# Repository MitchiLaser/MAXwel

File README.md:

# MAXwel

**MAX ii Workbench for Education and Learning - MAXwel**

MAXwel is a cheap and simple FPGA development board made for educational purposes.
It is based in a low-cost Altera MAX ii Chip (EPM240), containing 240 logic elements, 8Kbits of RAM and 32Kbits of flash memory.
The board is equipped with 8 switches, 4 push-buttons, 16 LEDs (divided into rows A and B of 8 LEDs each) and four 7-segment displays.
It also contains a 50MHz oscillator and a 14,7456 MHz oscillator as a clock source.
The board is programmed through a USB Blaster JTAG interface with the pin-header located on the board.

All schematics and PCB files are available in the `hardware` directory.

## Documentation and project template

[The user documentation is available in the `docs` directory](docs/main.pdf) and on the [landing page](https://mitchilaser.github.io/MAXwel/).

A [template for an empty VHDL project](template/vhdl) with correct pin assignments is available [in the `template` directory](template/).
The directory also contains a [template for a schematic based circuit design](template/schematic).
All templates are intended to be used with the [Quartus](https://fpgasoftware.intel.com/) software from Intel.

## What else?

There are also some features for hardcore enthusiasts.

### Lab Course

My university uses this FPGA board for a students lab course. There is a directory containing the reference designs for the lab course exercises.
The lab course exercises require the students to draw schematic diagrams in the Quartus software within a predefined template file.
The [Quartus](https://fpgasoftware.intel.com/) software only offers the logic symbols in the US style within the schematic editor.
This directory also offers EU style symbols for the project symbol library of the Quartus software.

### Overlay

**This project is currently under heavy development.**

The Overlay is an open FPGA architecture for open tools and user designs that is intended to run on the MAX ii chip, in essence an "FPGA on a FPGA".
The main goal of the Overlay is to provide a simple and easy to use platform for learning and experimenting with FPGA synthesis technology. 
Once the overlay is synthesizes and loaded into the MAX ii chip, it will be possible to load user designs into the overlay, without the need to re-synthesize the overlay itself.
This allows for a high level of flexibility and experimentation, as well as a way to learn about FPGA synthesis and design without the need for the closed source tools from the FPGA manufacturer.
Emulating an FPGA inside an FPGA takes up a lot of resources. Therefore the Overlay is not made for practical use cases outside of learning and experimentation.

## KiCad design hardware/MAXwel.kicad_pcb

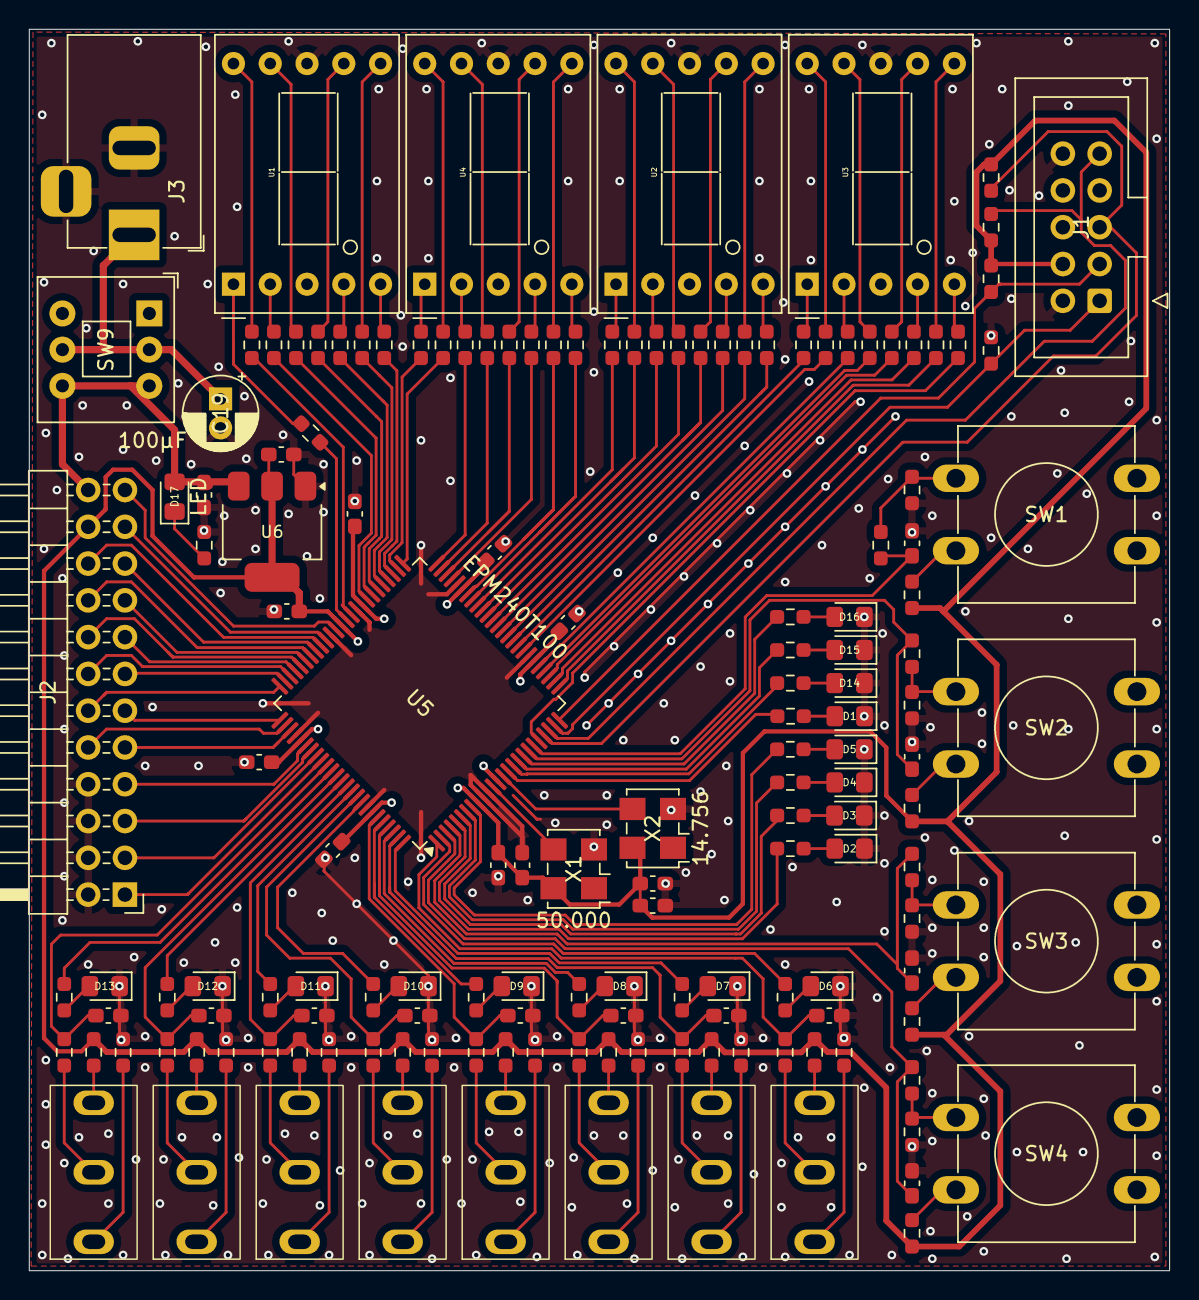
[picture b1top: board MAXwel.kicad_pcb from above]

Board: 2 copper layers, 78.7 x 85.7 mm, 155 parts (0 on the bottom side), 169 nets.

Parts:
C1, C2, C4, C5, C6, C7, C8, C10, C11, C12, C24: 100n; C_0603_1608Metric_Pad1.08x0.95mm_HandSolder
C3, C9, C13, C14, C15, C16, C17, C18, C20, C21, C22, C23: 20n; C_0603_1608Metric_Pad1.08x0.95mm_HandSolder
C19: 100µF; CP_Radial_D5.0mm_P2.00mm
C25: 47n; C_0603_1608Metric_Pad1.08x0.95mm_HandSolder
D1, D2, D3, D4, D5, D6, D7, D8, D9, D10, D11, D12, D13, D14, D15, D16, D17: LED; LED_0805_2012Metric_Pad1.15x1.40mm_HandSolder
J1: Conn_02x05_Odd_Even; IDC-Header_2x05_P2.54mm_Vertical
J2: Conn_02x12_Counter_Clockwise; PinHeader_2x12_P2.54mm_Horizontal
J3: Barrel_Jack_Switch_Pin3Ring; BarrelJack_Horizontal
R1, R2, R3, R4, R5, R30, R31, R32, R33, R43, R46, R49, R51, R52, R53, R54, R55, R56, R57, R58, R59, R62, R63, R65, R66, R67, R71, R72, R73, R74, R75, R76, R77, R82, R83, R84, R85, R86, R87, R88, R89: 10K; R_0603_1608Metric_Pad0.98x0.95mm_HandSolder
R6, R7, R8, R9, R10, R11, R12, R13, R14, R15, R16, R17, R18, R19, R20, R21, R22, R23, R24, R25, R26, R27, R28, R29, R34, R35, R36, R37, R38, R39, R40, R41: 470; R_0603_1608Metric_Pad0.98x0.95mm_HandSolder
R42, R44, R45, R47, R48, R50, R60, R61, R64, R68, R69, R70, R78, R79, R80, R81: 1K; R_0603_1608Metric_Pad0.98x0.95mm_HandSolder
SW1, SW2, SW3, SW4: SW_Push_Dual; SW_PUSH-12mm
SW5, SW6, SW7, SW8, SW10, SW11, SW12, SW13: SW_Wuerth_450301014042; SW_Slide_SPDT_Straight_12.8mm_6.9mm
SW9: SW_Push_DPDT; SW_Push_2P2T_Toggle_CK_PVA2OAH5xxxxxxV2
U1, U2, U3, U4: D168K; D1X8K
U5: EPM240T100; TQFP-100_14x14mm_P0.5mm
U6: AMS1117-3.3; SOT-223-3_TabPin2
X1: 50.000; Oscillator_SMD_EuroQuartz_XO53-4Pin_5.0x3.2mm_HandSoldering
X2: 14.756; Oscillator_SMD_EuroQuartz_XO53-4Pin_5.0x3.2mm_HandSoldering

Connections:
+3V3: C1.1, C2.1, C4.1, C5.1, C6.1, C7.1, C8.1, C10.1, C11.1, C12.1, C25.1, J1.4, J2.22, R30.2, R31.2, R32.2, R44.2, R47.2, R60.2, R61.2, R66.2, R71.2, R73.2, R75.2, R82.2, R84.2, R86.2, R88.2, U5.9 (VCCIO1), U5.13 (VCCINT), U5.31 (VCCIO1), U5.45 (VCCIO1), U5.59 (VCCIO2), U5.63 (VCCINT), U5.80 (VCCIO2), U5.94 (VCCIO2), U6.2 (VO), X1.4 (V+), X2.4 (V+)
+5V: C24.1, D17.2 (A), J2.24, SW9.3 (C), SW9.6 (C), U6.3 (VI)
Bridge_1: R41.2, U5.52 (IO2_52)
GND: C1.2, C2.2, C3.2, C4.2, C5.2, C6.2, C7.2, C8.2, C9.2, C10.2, C11.2, C12.2, C13.2, C14.2, C15.2, C16.2, C17.2, C18.2, C19.2, C20.2, C21.2, C22.2, C23.2, C24.2, C25.2, D1.1 (K), D2.1 (K), D3.1 (K), D4.1 (K), D5.1 (K), D6.1 (K), D7.1 (K), D8.1 (K), D9.1 (K), D10.1 (K), D11.1 (K), D12.1 (K), D13.1 (K), D14.1 (K), D15.1 (K), D16.1 (K), J1.2, J1.10, J2.2, J2.4, J2.6, J2.8, J3.2, J3.3, R33.1, R43.1, R46.1, R49.1, R51.1, R67.2, R72.2, R74.2, R76.2, R77.1, R83.2, R85.2, R87.2, R89.2, U1.3 (CC), U1.8 (CC), U2.3 (CC), U2.8 (CC), U3.3 (CC), U3.8 (CC), U4.3 (CC), U4.8 (CC), U5.10 (GNDIO), U5.11 (GNDINT), U5.32 (GNDIO), U5.46 (GNDIO), U5.60 (GNDIO), U5.65 (GNDINT), U5.79 (GNDIO), U5.93 (GNDIO), U6.1 (GND), X1.2 (GND), X2.2 (GND)
unnamed: C19.1, J3.1, SW9.2 (B), SW9.5 (B)
unnamed: D1.2 (A), R1.2
unnamed: D2.2 (A), R2.2
unnamed: D3.2 (A), R3.2
unnamed: D4.2 (A), R4.2
unnamed: D5.2 (A), R5.2
unnamed: D6.2 (A), R52.2
unnamed: D7.2 (A), R53.2
unnamed: D8.2 (A), R54.2
unnamed: D9.2 (A), R55.2
unnamed: D10.2 (A), R56.2
unnamed: D11.2 (A), R57.2
unnamed: D12.2 (A), R58.2
unnamed: D13.2 (A), R59.2
unnamed: D14.2 (A), R62.2
unnamed: D15.2 (A), R63.2
unnamed: D16.2 (A), R65.2
unnamed: D17.1 (K), R77.2
unnamed: J1.1, R33.2, U5.24 (TCK)
unnamed: J1.3, R32.1, U5.25 (TDO)
unnamed: J1.5, R30.1, U5.22 (TMS)
unnamed: J1.9, R31.1, U5.23 (TDI)
unnamed: J2.1, U5.84 (IO2_84)
unnamed: J2.3, U5.83 (IO2_83)
unnamed: J2.5, U5.82 (IO2_82)
unnamed: J2.7, U5.81 (IO2_81)
unnamed: J2.9, U5.78 (IO2_78)
unnamed: J2.10, U5.77 (IO2_77)
unnamed: J2.11, U5.76 (IO2_76)
unnamed: J2.12, U5.75 (IO2_75)
unnamed: J2.13, U5.74 (IO2_74)
unnamed: J2.14, U5.73 (IO2_73)
unnamed: J2.15, U5.72 (IO2_72)
unnamed: J2.16, U5.71 (IO2_71)
unnamed: J2.17, U5.70 (IO2_70)
unnamed: J2.18, U5.69 (IO2_69)
unnamed: J2.19, U5.68 (IO2_68)
unnamed: J2.20, U5.67 (IO2_67)
unnamed: J2.21, U5.66 (IO2_66)
unnamed: J2.23, U5.64 (IO2_64/GCLK3)
unnamed: R42.2, R43.2, SW1.1, SW1.3
unnamed: R44.1, SW1.2, SW1.4
unnamed: R45.2, R46.2, SW2.1, SW2.3
unnamed: R47.1, SW2.2, SW2.4
unnamed: R48.2, R49.2, SW3.1, SW3.3
unnamed: R50.2, R51.2, SW4.1, SW4.3
unnamed: R60.1, SW3.2, SW3.4
unnamed: R61.1, SW4.2, SW4.4
unnamed: R66.1, SW5.3 (A)
unnamed: R64.2, SW5.1 (B)
unnamed: R67.1, SW5.2 (C)
unnamed: R71.1, SW6.3 (A)
unnamed: R68.2, SW6.1 (B)
unnamed: R72.1, SW6.2 (C)
unnamed: R73.1, SW7.3 (A)
unnamed: R69.2, SW7.1 (B)
unnamed: R74.1, SW7.2 (C)
unnamed: R75.1, SW8.3 (A)
unnamed: R70.2, SW8.1 (B)
unnamed: R76.1, SW8.2 (C)
unnamed: R82.1, SW10.3 (A)
unnamed: R78.2, SW10.1 (B)
unnamed: R83.1, SW10.2 (C)
unnamed: R84.1, SW11.3 (A)
unnamed: R79.2, SW11.1 (B)
unnamed: R85.1, SW11.2 (C)
unnamed: R86.1, SW12.3 (A)
unnamed: R80.2, SW12.1 (B)
unnamed: R87.1, SW12.2 (C)
unnamed: R88.1, SW13.3 (A)
unnamed: R81.2, SW13.1 (B)
unnamed: R89.1, SW13.2 (C)
unnamed: R9.1, U1.7 (A)
unnamed: R7.1, U1.6 (B)
unnamed: R8.1, U1.4 (C)
unnamed: R11.1, U1.2 (D)
unnamed: R6.1, U1.5 (DP)
unnamed: R13.1, U1.1 (E)
unnamed: R10.1, U1.9 (F)
unnamed: R12.1, U1.10 (G)
unnamed: R17.1, U2.7 (A)
unnamed: R15.1, U2.6 (B)
unnamed: R16.1, U2.4 (C)
unnamed: R19.1, U2.2 (D)
unnamed: R14.1, U2.5 (DP)
unnamed: R21.1, U2.1 (E)
unnamed: R18.1, U2.9 (F)
unnamed: R20.1, U2.10 (G)
unnamed: R25.1, U3.7 (A)
unnamed: R23.1, U3.6 (B)
unnamed: R24.1, U3.4 (C)
unnamed: R27.1, U3.2 (D)
unnamed: R22.1, U3.5 (DP)
unnamed: R29.1, U3.1 (E)
unnamed: R26.1, U3.9 (F)
unnamed: R28.1, U3.10 (G)
unnamed: R37.1, U4.7 (A)
unnamed: R35.1, U4.6 (B)
unnamed: R36.1, U4.4 (C)
unnamed: R39.1, U4.2 (D)
unnamed: R34.1, U4.5 (DP)
unnamed: R41.1, U4.1 (E)
unnamed: R38.1, U4.9 (F)
unnamed: R40.1, U4.10 (G)
unnamed: R52.1, U5.2 (IO1_2)
unnamed: C14.1, R50.1, U5.3 (IO1_3)
unnamed: C13.1, R48.1, U5.4 (IO1_4)
unnamed: R2.1, U5.5 (IO1_5)
unnamed: R3.1, U5.6 (IO1_6)
unnamed: R4.1, U5.7 (IO1_7)
unnamed: R5.1, U5.8 (IO1_8)
unnamed: U5.12 (IO1_12/GCLK0), X1.3 (OUT)
unnamed: U5.14 (IO1_14/GCLK1), X2.3 (OUT)
unnamed: R1.1, U5.15 (IO1_15)
unnamed: R62.1, U5.16 (IO1_16)
unnamed: R63.1, U5.17 (IO1_17)
unnamed: R65.1, U5.18 (IO1_18)
unnamed: C9.1, R45.1, U5.19 (IO1_19)
unnamed: C3.1, R42.1, U5.20 (IO1_20)
unnamed: R22.2, U5.21 (IO1_21)
unnamed: R23.2, U5.26 (IO1_26)
unnamed: R24.2, U5.27 (IO1_27)
unnamed: R25.2, U5.28 (IO1_28)
unnamed: R26.2, U5.29 (IO1_29)
unnamed: R27.2, U5.30 (IO1_30)
unnamed: R28.2, U5.33 (IO1_33)
unnamed: R29.2, U5.34 (IO1_34)
unnamed: R14.2, U5.35 (IO1_35)
unnamed: R15.2, U5.36 (IO1_36)
unnamed: R16.2, U5.37 (IO1_37)
unnamed: R17.2, U5.38 (IO1_38)
unnamed: R18.2, U5.39 (IO1_39)
unnamed: R19.2, U5.40 (IO1_40)
unnamed: R20.2, U5.41 (IO1_41)
unnamed: R21.2, U5.42 (IO1_42)
unnamed: R34.2, U5.43 (IO1_43/DEV_OE)
unnamed: R35.2, U5.44 (IO1_44/DEV_CLRn)
unnamed: R36.2, U5.47 (IO1_47)
unnamed: R37.2, U5.48 (IO1_48)
unnamed: R38.2, U5.49 (IO1_49)
unnamed: R39.2, U5.50 (IO1_50)
unnamed: R40.2, U5.51 (IO1_51)
unnamed: C15.1, R64.1, U5.1 (IO2_1)
unnamed: R6.2, U5.53 (IO2_53)
unnamed: R7.2, U5.54 (IO2_54)
unnamed: R8.2, U5.55 (IO2_55)
unnamed: R9.2, U5.56 (IO2_56)
unnamed: R10.2, U5.57 (IO2_57)
unnamed: R11.2, U5.58 (IO2_58)
unnamed: R12.2, U5.61 (IO2_61)
unnamed: R13.2, U5.62 (IO2_62/GCLK2)
unnamed: C16.1, R68.1, U5.85 (IO2_85)
unnamed: R59.1, U5.86 (IO2_86)
unnamed: C17.1, R69.1, U5.87 (IO2_87)
unnamed: R58.1, U5.88 (IO2_88)
unnamed: C20.1, R78.1, U5.89 (IO2_89)
unnamed: R57.1, U5.90 (IO2_90)
unnamed: C21.1, R79.1, U5.91 (IO2_91)
unnamed: R56.1, U5.92 (IO2_92)
unnamed: C23.1, R81.1, U5.95 (IO2_95)
unnamed: R55.1, U5.96 (IO2_96)
unnamed: C22.1, R80.1, U5.97 (IO2_97)
unnamed: R54.1, U5.98 (IO2_98)
unnamed: C18.1, R70.1, U5.99 (IO2_99)
unnamed: R53.1, U5.100 (IO2_100)

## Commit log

2024-06-05 all leds placed on the board
2024-06-05 restructure + buttons added
2024-06-06 restructured » more Space
2024-06-06 all objects placed, footprint assignment missing
2024-06-06 all footprints assigned
2024-06-06 ERC applied and fixed missing power flags
2024-06-07 started routing
2024-06-07 pcb outline defined, ready for autorouter test
2024-06-07 partially done 1/4
2024-06-07 nearly done
2024-06-07 last attempt to autorouter
2024-06-07 routing done
2024-06-07 cleanup pcb design
2024-06-07 replaced GND traces on backside with ground plane
2024-06-08 established ground planes
2024-06-08 remove reference from silkscreen
2024-06-08 put values on silk screen
2024-06-08 first production run
2024-06-08 fixed wrong part number
2024-06-10 fill README with content + Rename project
2024-06-10 create overlay project + Logic Cell implementation
2024-06-11 update License
2024-06-11 overlay description
2024-06-16 updated gitignore and workflows for automatic documentation
2024-06-17 overlay: unused pins default changed
2024-06-17 created template for documentation
2024-06-18 uniform naming
2024-06-18 documentation written
2024-06-18 fixed missing backslash in SVG causing LaTeX to abort compilation.
2024-06-19 Makefile: remove LaTeX files when calling clean target
2024-06-19 include pdf in docs
2024-06-19 provide template project
2024-06-19 starting with landingpage and restructuring templates
2024-06-19 landing page for gh pages
2024-06-19 update README » landing page
2024-06-19 empty template for schematic project
2024-06-19 add new template to docs
2024-06-19 fixed missing file in schematics template
2024-06-20 fixed wrong footprint for slide switches
2024-06-25 added configuration shift register in LC and also testing with 4 LCs
2024-06-27 overlay: instantiate groups of LCs with 2 parameters
2024-06-29 overlay: remove mixing of one-indexed and zero-indexed vectors
2024-06-30 overlay_ change to ring structure
2024-07-22 change resistor and capacitor size, rearrange pinheader and 7-seg connections
2024-07-23 rotation of FPGA
2024-07-23 arranged mostly all parts to reduce intersections
2024-07-23 switches: R and C placement optimized
2024-07-23 3/4 of components routed on single layer
2024-07-23 shifted everything 1 pin to the side for better power routing
2024-07-24 first successfull redesign
2024-07-24 squashing pcb layout
2024-07-24 JTAG interface: increase spacing, add more GND for better EMI
2024-07-29 optimized traces
2024-07-29 set part visibility + fabrication files
2024-08-02 update sw_slide footprint, added part references and QR code on backside
2024-08-07 README: project status update
2024-08-14 new prorotype version: update pin assignment in template project
2024-08-14 added clock constraints
2024-08-14 update pin mapping to match new design
2024-08-14 update docs so anybody can replicate the device
2024-08-16 added missing assignments and documentation for 7-Segments
2024-08-16 update docs and Readme
2024-08-17 added bin2hex example project
2024-08-17 led_blink example project
2024-08-17 dice example project
2024-08-17 added quick start guide to docs
2024-08-19 added missing component number
2024-08-21 added information about non-working USB blasters in docs
2024-10-07 menubar: placed icons, missing functionality
2024-10-10 removed resistors at sliding switches, 5mm smaller circuit board
2024-10-10 tighter layout
2024-10-11 Added ClockDivider symbol to template project and created reference schematics for (almost) all exercises
2024-10-14 added reference designs for lab curse
2024-10-14 adjust template design for lab curse
2024-10-14 gateway button background
2024-10-23 Quartus EU symbol patch
2024-10-23 restructure lab curse
2024-10-24 added resizeable menu bar on the right side
2024-10-24 light modifications, nothing important
2024-10-24 fix: install script for quartus symbols failed, wrong #!
2024-10-30 fixed annoying typo, had to make changes nearly everywhere
2024-12-23 add PCB data
2025-01-22 Quartus EU patch not working any more -> change to project-specific symbols in lab-cource template
2025-01-22 fixed template project for lab curse: provide also GND, VCC and JK-FF symbols
2025-01-23 changes in template: use shift register with inverted clock input
2025-02-07 add new schematic symbols to template library
2025-02-07 update reference designs and include 3-input nand in symbol lib
2025-02-07 template: add half and full adder
2025-02-07 provide reference schematics in eu and us style symbols
2025-10-02 lab curse: update symbol table
2025-10-08 Update names to be equal in docs and template
2025-10-08 ghpages: update index
2025-10-08 ghpages: update picture
2025-10-15 update lab course template: added RS and RST FF
2025-11-24 fix template
2025-11-24 fix 4MUX Input names
